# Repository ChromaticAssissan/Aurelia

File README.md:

HEAD
\# Aurelia Upper Ocean Profiler

A custom variable buoyancy ocean profiling system developed at UMass Dartmouth.

\## Features

\- Arduino-based motherboard

\- Sensor integration

\- Wireless communication

\- Variable buoyancy control

\- Custom PCB development

\## Author

Frankie Bouchard

=======
# Aurelia
The design of the control boards for the Aurelia ocean profilier
2aa0dd996f78106de7114200720a692faca2b326

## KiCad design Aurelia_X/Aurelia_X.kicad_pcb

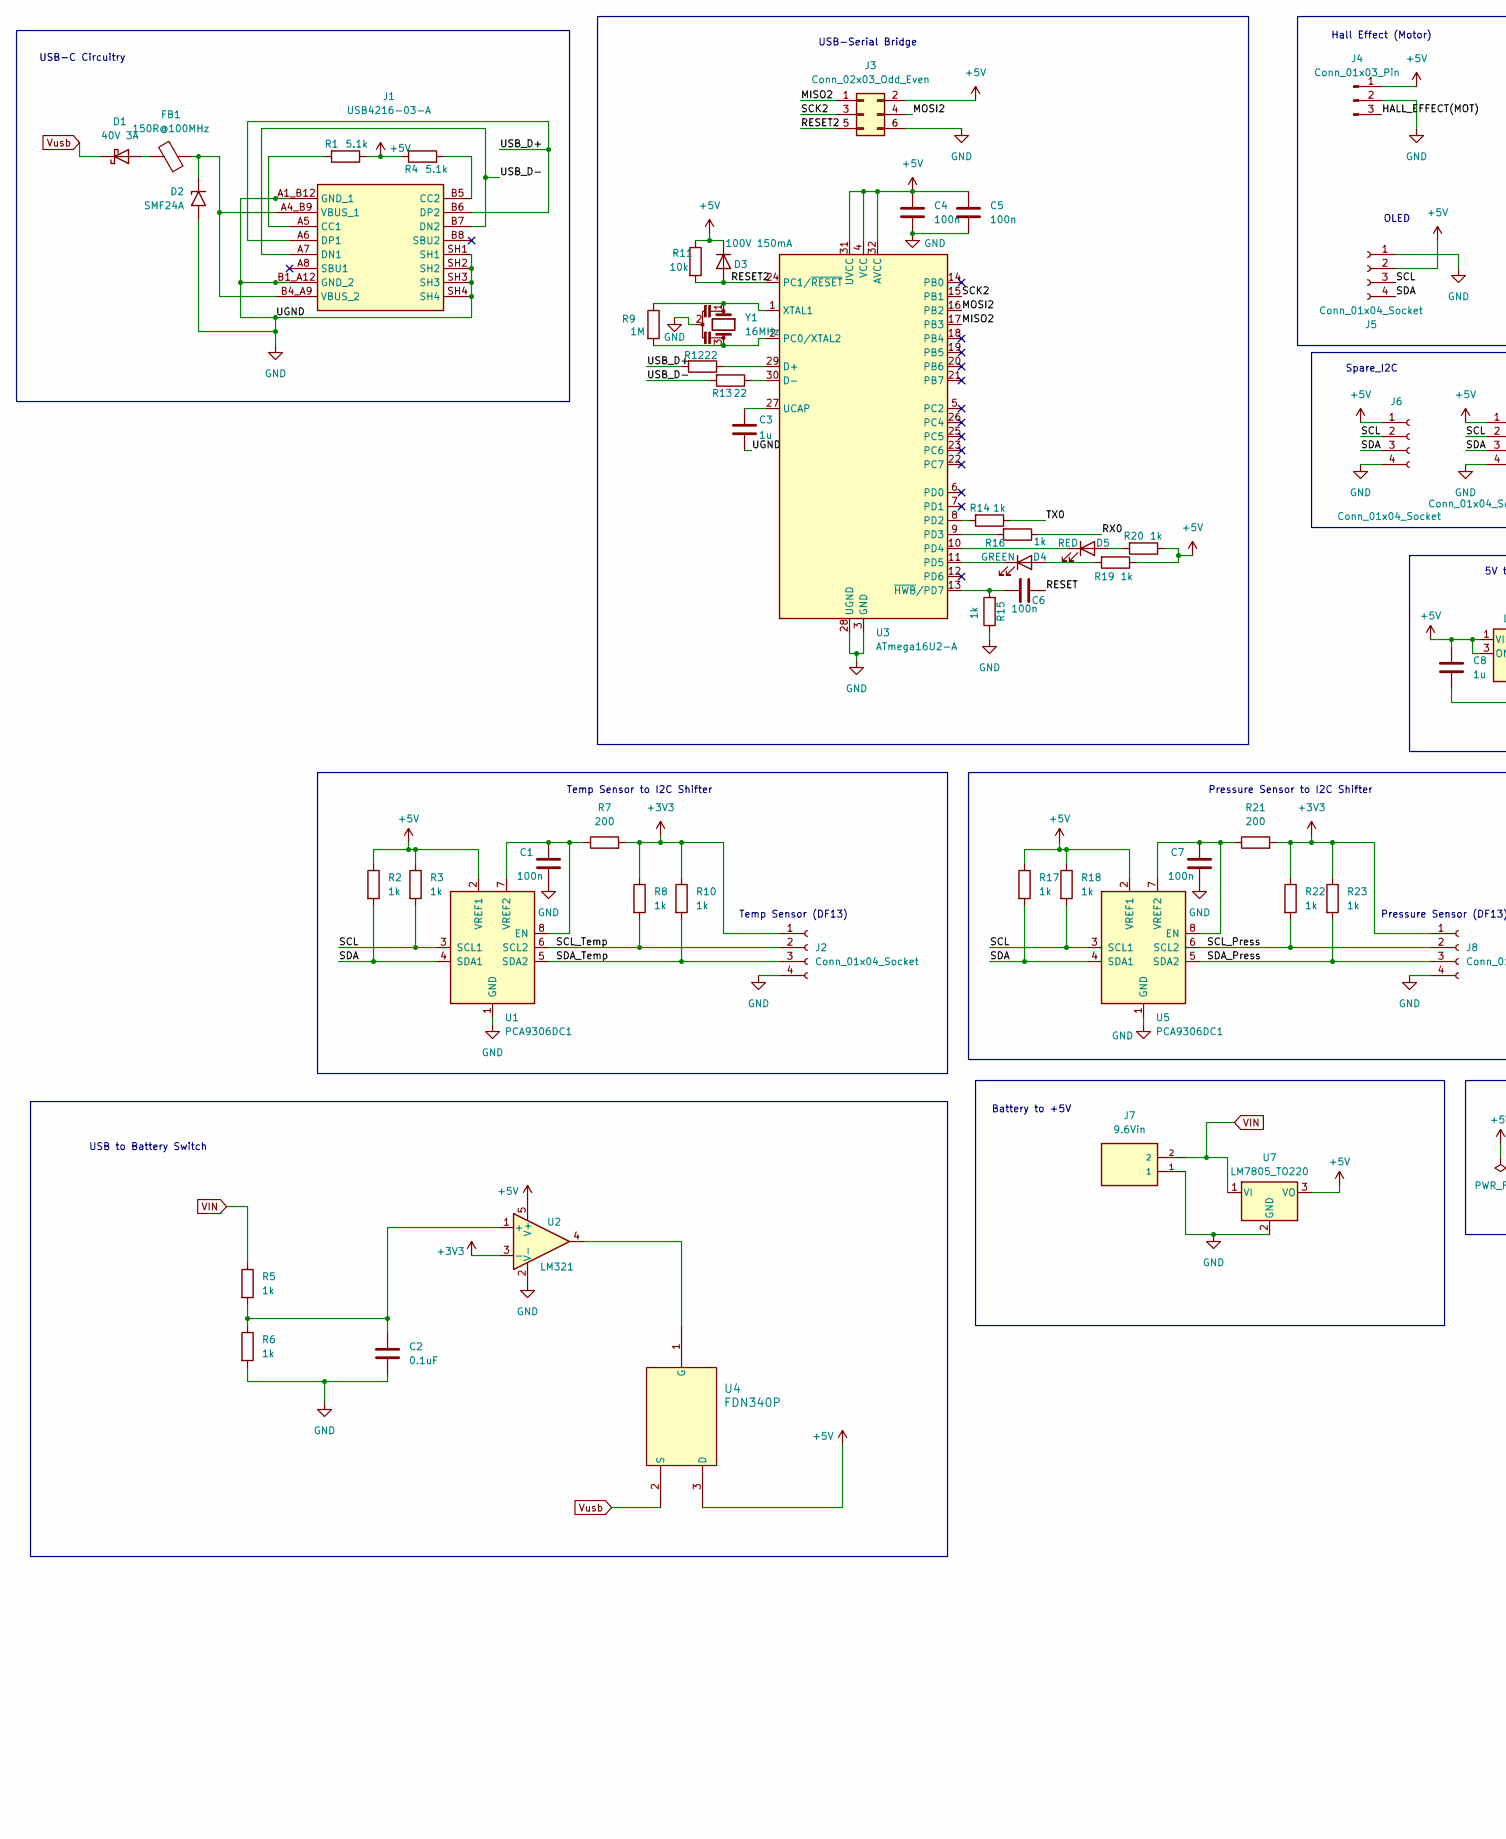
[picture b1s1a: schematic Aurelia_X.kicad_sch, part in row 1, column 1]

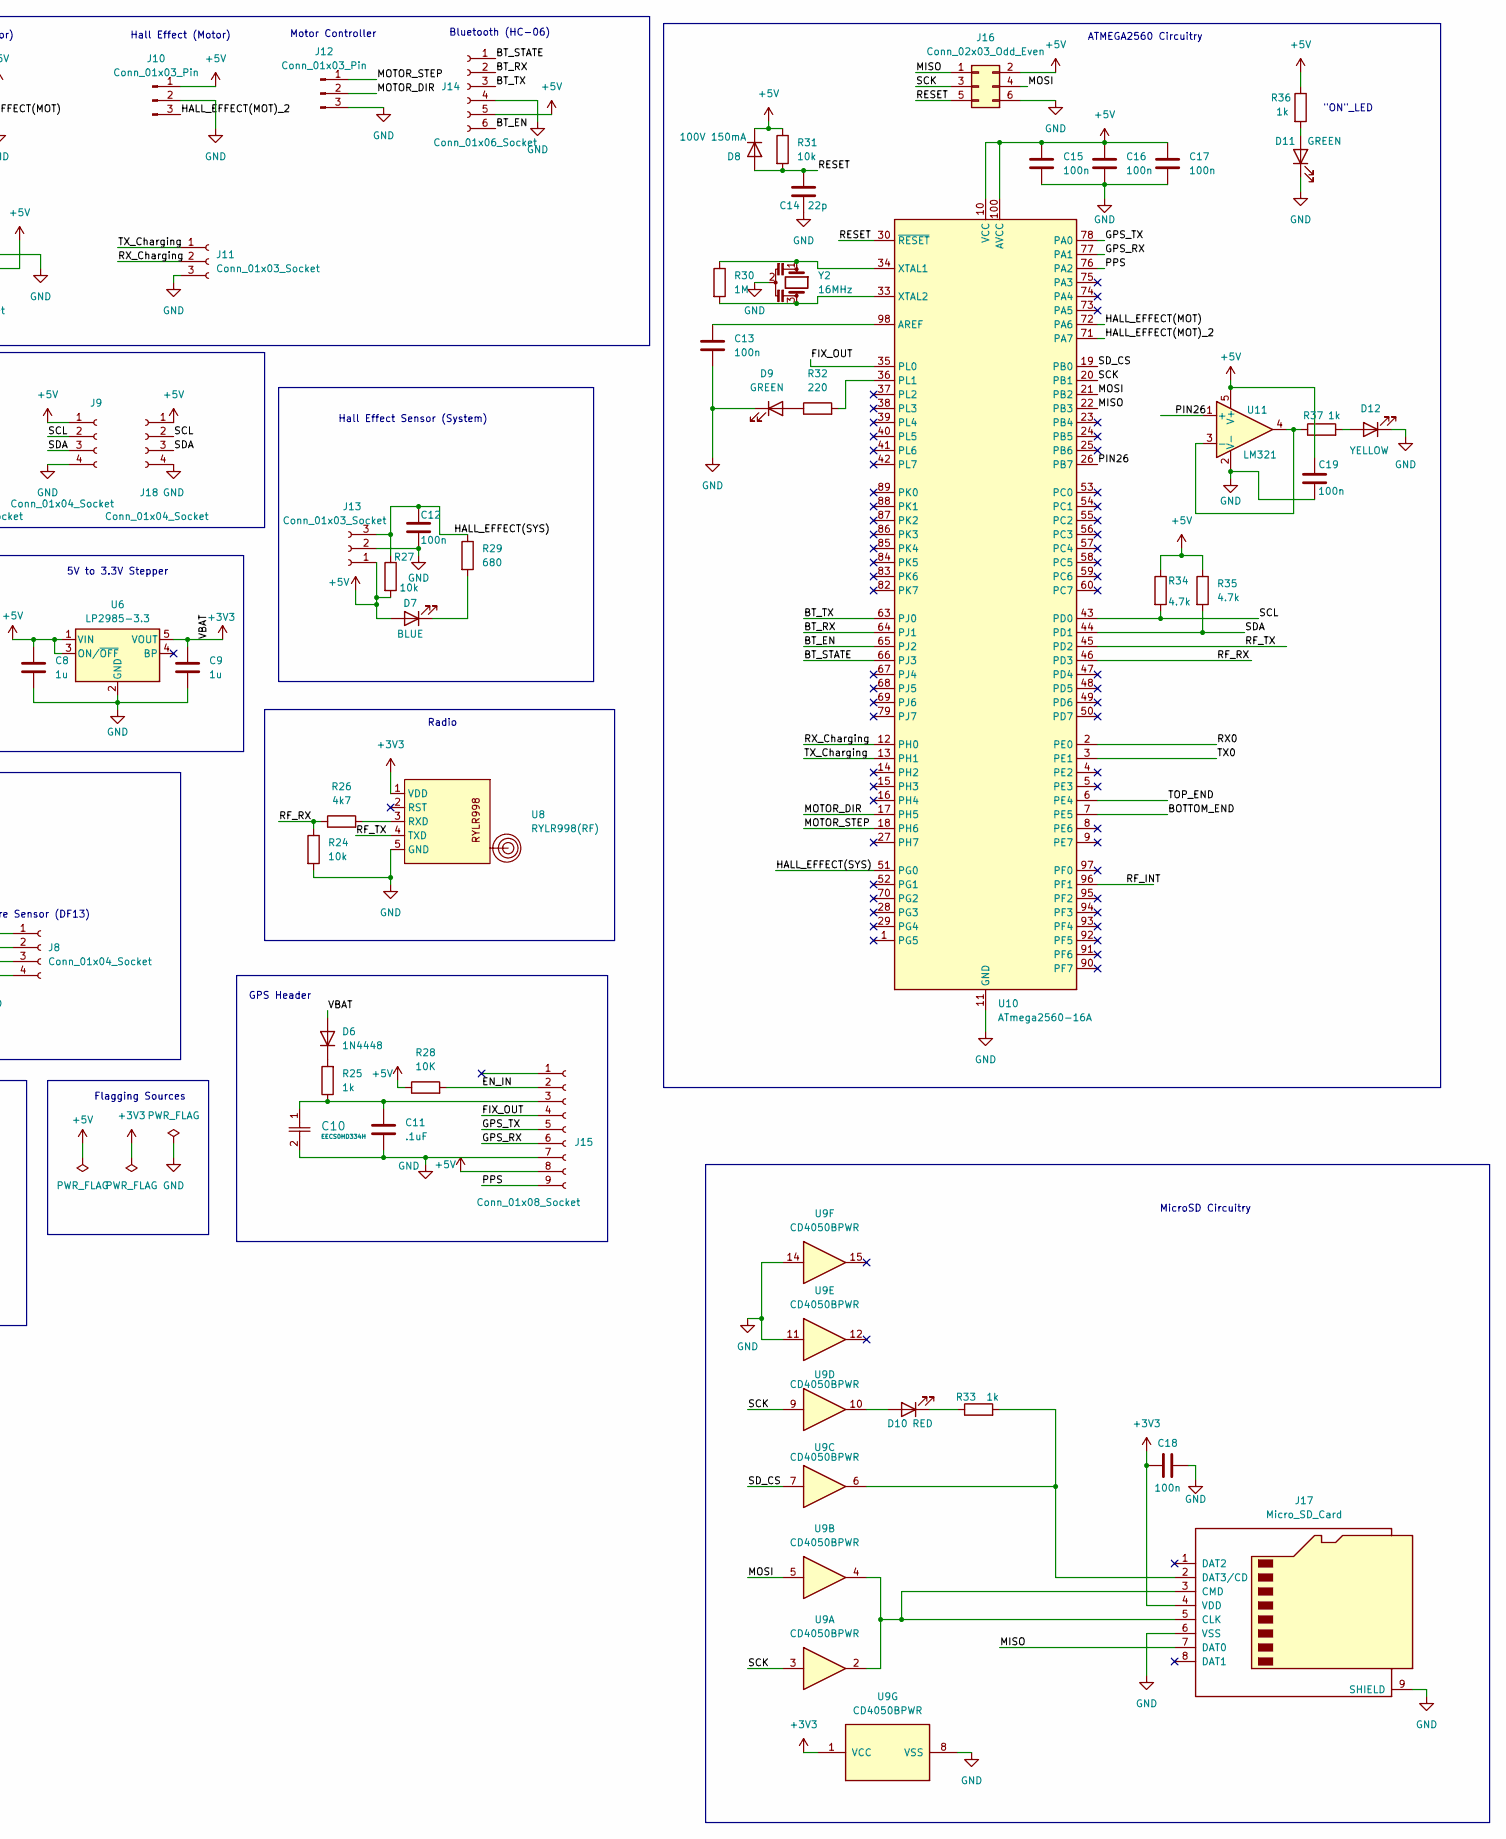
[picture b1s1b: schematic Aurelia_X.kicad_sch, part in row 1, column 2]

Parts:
C1, C4, C5, C6, C7, C12, C13, C15, C16, C17, C18, C19: 100n; C_0603_1608Metric_Pad1.08x0.95mm_HandSolder
C2: 0.1uF; C_0603_1608Metric_Pad1.08x0.95mm_HandSolder
C3, C8, C9: 1u; C_0603_1608Metric_Pad1.08x0.95mm_HandSolder
C10: EECS0HD334H; SUP_CAP_EECSD_H_PAN
C11: .1uF; C_0603_1608Metric_Pad1.08x0.95mm_HandSolder
C14: 22p; C_0603_1608Metric_Pad1.08x0.95mm_HandSolder
D1: 40V 3A; 40V_3A_SMA_SHKY_DIODE
D2: SMF24A; D_SMF
D3, D8: 100V 150mA; D_SOD-123
D4, D9, D11: GREEN; LED_0603_1608Metric_Pad1.05x0.95mm_HandSolder
D5, D10: RED; LED_0603_1608Metric_Pad1.05x0.95mm_HandSolder
D6: 1N4448; D_SOD-323F
D7: BLUE; LED_0603_1608Metric_Pad1.05x0.95mm_HandSolder
D12: YELLOW; LED_0603_1608Metric_Pad1.05x0.95mm_HandSolder
FB1: 150R@100MHz; R_0805_2012Metric_Pad1.20x1.40mm_HandSolder
J1: USB4216-03-A; GCT_USB4216-03-A_REVA; Mouser Part Number 640-USB4216-03-A
J2, J8: Conn_01x04_Socket; DF13_4P_125DS_25
J3, J16: Conn_02x03_Odd_Even; PinHeader_2x03_P2.54mm_Vertical
J4, J10, J12: Conn_01x03_Pin; PinHeader_1x03_P2.54mm_Vertical
J5: Conn_01x04_Socket; PinSocket_1x04_P2.54mm_Vertical
J6, J9, J18: Conn_01x04_Socket; JST_XA_S04B-XASK-1N-BN_1x04_P2.50mm_Horizontal
J7: 9.6Vin; 691137710002
J11: Conn_01x03_Socket; PinHeader_1x03_P2.54mm_Vertical
J13: Conn_01x03_Socket; PinSocket_1x03_P2.54mm_Vertical
J14: Conn_01x06_Socket; PinSocket_1x06_P2.54mm_Vertical
J15: Conn_01x08_Socket; PinSocket_1x09_P2.54mm_Vertical
J17: Micro_SD_Card; microSD_HC_Hirose_DM3BT-DSF-PEJS
R1, R4: 5.1k; R_0603_1608Metric_Pad0.98x0.95mm_HandSolder
R2, R3, R5, R6, R8, R10, R14, R15, R16, R17, R18, R19, R20, R22, R23, R25, R33, R36, R37: 1k; R_0603_1608Metric_Pad0.98x0.95mm_HandSolder
R7, R21: 200; R_0603_1608Metric_Pad0.98x0.95mm_HandSolder
R9, R30: 1M; R_0603_1608Metric_Pad0.98x0.95mm_HandSolder
R11, R24, R27, R31: 10k; R_0603_1608Metric_Pad0.98x0.95mm_HandSolder
R12, R13: 22; R_0603_1608Metric_Pad0.98x0.95mm_HandSolder
R26: 4k7; R_0603_1608Metric_Pad0.98x0.95mm_HandSolder
R28: 10K; R_0603_1608Metric_Pad0.98x0.95mm_HandSolder
R29: 680; R_0603_1608Metric_Pad0.98x0.95mm_HandSolder
R32: 220; R_0603_1608Metric_Pad0.98x0.95mm_HandSolder
R34, R35: 4.7k; R_0603_1608Metric_Pad0.98x0.95mm_HandSolder
U1, U5: PCA9306DC1; VSSOP-8_2.3x2mm_P0.5mm
U2, U11: LM321; SOT-23-5
U3: ATmega16U2-A; TQFP-32_7x7mm_P0.8mm
U4: FDN340P; SOT-23
U6: LP2985-3.3; SOT-23-5_HandSoldering
U7: LM7805_TO220; TO-220-3_Vertical
U8: RYLR998(RF); PinSocket_1x05_P2.54mm_Horizontal
U9: CD4050BPWR; SOIC-16_3.9x9.9mm_P1.27mm
U10: ATmega2560-16A; TQFP-100_14x14mm_P0.5mm
Y1, Y2: 16MHz; Resonator_Murata_CSTLSxxxX-3Pin_W5.5mm_H3.0mm

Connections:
+3V3: C9.1, C18.1, D6.2 (A), J2.1, J8.1, J17.4 (VDD), R7.2, R8.1, R10.1, R21.2, R22.1, R23.1, U2.3 (-), U6.5 (VOUT), U8.1 (VDD), U9.1 (VCC)
+5V: C4.1, C5.1, C8.1, C15.1, C16.1, C17.1, C19.1, D3.1 (K), D7.2 (A), D8.1 (K), J3.2, J4.1, J5.2, J6.1, J9.1, J10.1, J13.1, J14.5, J15.8, J16.2, J18.1, R1.1, R2.1, R3.1, R4.1, R11.1, R17.1, R18.1, R19.1, R20.1, R27.2, R28.1, R31.1, R34.1, R35.1, R36.1, U1.2 (VREF1), U2.5 (V+), U3.4 (VCC), U3.31 (UVCC), U3.32 (AVCC), U4.3 (D), U5.2 (VREF1), U6.1 (VIN), U6.3 (ON/~OFF), U7.3 (VO), U10.10 (VCC), U10.31 (VCC), U10.61 (VCC), U10.80 (VCC), U10.100 (AVCC), U11.5 (V+)
/BOTTOM_END: U10.7 (PE5)
/BT_EN: J14.6, U10.65 (PJ2)
/BT_RX: J14.2, U10.64 (PJ1)
/BT_STATE: J14.1, U10.66 (PJ3)
/BT_TX: J14.3, U10.63 (PJ0)
/EN_IN: J15.2, R28.2
/FIX_OUT: J15.4, U10.35 (PL0)
/GPS_RX: J15.6, U10.77 (PA1)
/GPS_TX: J15.5, U10.78 (PA0)
/HALL_EFFECT(MOT): J4.3, U10.72 (PA6)
/HALL_EFFECT(MOT)_2: J10.3, U10.71 (PA7)
/HALL_EFFECT(SYS): C12.1, J13.3, R27.1, R29.1, U10.51 (PG0)
/MISO: J16.1, J17.7 (DAT0), U10.22 (PB3)
/MISO2: J3.1, U3.17 (PB3)
/MOSI: J16.4, U9.5, U10.21 (PB2)
/MOSI2: J3.4, U3.16 (PB2)
/MOTOR_DIR: J12.2, U10.17 (PH5)
/MOTOR_STEP: J12.1, U10.18 (PH6)
/PIN26: U10.26 (PB7), U11.1 (+)
/PPS: J15.9, U10.76 (PA2)
/RESET: C6.1, C14.1, D8.2 (A), J16.5, R31.2, U10.30 (~RESET)
/RESET2: D3.2 (A), J3.5, R11.2, U3.24 (PC1/~RESET)
/RF_INT: U10.96 (PF1)
/RF_RX: R24.1, R26.1, U10.46 (PD3)
/RF_TX: U8.4 (TXD), U10.45 (PD2)
/RX0: R16.1, U10.2 (PE0)
/RX_Charging: J11.2, U10.12 (PH0)
/SCK: J16.3, U9.3, U9.9, U10.20 (PB1)
/SCK2: J3.3, U3.15 (PB1)
/SCL: J5.3, J6.2, J9.2, J18.2, R3.2, R18.2, R34.2, U1.3 (SCL1), U5.3 (SCL1), U10.43 (PD0)
/SCL_Press: J8.2, R22.2, U5.6 (SCL2)
/SCL_Temp: J2.2, R8.2, U1.6 (SCL2)
/SDA: J5.4, J6.3, J9.3, J18.3, R2.2, R17.2, R35.2, U1.4 (SDA1), U5.4 (SDA1), U10.44 (PD1)
/SDA_Press: J8.3, R23.2, U5.5 (SDA2)
/SDA_Temp: J2.3, R10.2, U1.5 (SDA2)
/SD_CS: U9.7, U10.19 (PB0)
/TOP_END: U10.6 (PE4)
/TX0: R14.1, U10.3 (PE1)
/TX_Charging: J11.1, U10.13 (PH1)
/USB_D+: J1.A6 (DP1), J1.B6 (DP2), R12.2
/USB_D-: J1.A7 (DN1), J1.B7 (DN2), R13.2
GND: C1.2, C2.2, C3.2, C4.2, C5.2, C7.2, C8.2, C9.2, C10.2, C11.2, C12.2, C13.2, C14.2, C15.2, C16.2, C17.2, C18.2, C19.2, D2.2 (A2), D9.1 (K), D11.1 (K), D12.1 (K), J1.A1_B12 (GND_1), J1.B1_A12 (GND_2), J1.SH1, J1.SH2, J1.SH3, J1.SH4, J2.4, J3.6, J4.2, J5.1, J6.4, J7.1, J8.4, J9.4, J10.2, J11.3, J12.3, J13.2, J14.4, J15.7, J16.6, J17.6 (VSS), J17.9 (SHIELD), J18.4, R6.2, R15.1, R24.2, U1.1 (GND), U2.2 (V-), U3.3 (GND), U3.28 (UGND), U5.1 (GND), U6.2 (GND), U7.2 (GND), U8.5 (GND), U9.8 (VSS), U9.11, U9.14, U10.11 (GND), U10.32 (GND), U10.62 (GND), U10.81 (GND), U10.99 (GND), U11.2 (V-), Y1.2, Y2.2
unnamed: D1.2 (A), FB1.2
unnamed: D2.1 (A1), FB1.1, J1.A4_B9 (VBUS_1), J1.B4_A9 (VBUS_2)
unnamed: D4.2 (A), R19.2
unnamed: D4.1 (K), U3.11 (PD5)
unnamed: D5.2 (A), R20.2
unnamed: D5.1 (K), U3.10 (PD4)
unnamed: D6.1 (K), R25.2
unnamed: D7.1 (K), R29.2
unnamed: D9.2 (A), R32.1
unnamed: D10.2 (A), U9.10
unnamed: D10.1 (K), R33.1
unnamed: D11.2 (A), R36.2
unnamed: D12.2 (A), R37.2
unnamed: J1.A5 (CC1), R1.2
unnamed: J1.B5 (CC2), R4.2
unnamed: C10.1, C11.1, J15.3, R25.1
unnamed: J17.3 (CMD), J17.5 (CLK), U9.2, U9.4
unnamed: J17.2 (DAT3/CD), R33.2, U9.6
unnamed: C1.1, R7.1, U1.7 (VREF2), U1.8 (EN)
unnamed: C2.1, R5.2, R6.1, U2.1 (+)
unnamed: R12.1, U3.29 (D+)
unnamed: R13.1, U3.30 (D-)
unnamed: R9.2, U3.2 (PC0/XTAL2), Y1.3
unnamed: R14.2, U3.8 (PD2)
unnamed: R16.2, U3.9 (PD3)
unnamed: C3.1, U3.27 (UCAP)
unnamed: R9.1, U3.1 (XTAL1), Y1.1
unnamed: C6.2, R15.2, U3.13 (~HWB/PD7)
unnamed: U2.4, U4.1 (G)
unnamed: C7.1, R21.1, U5.7 (VREF2), U5.8 (EN)
unnamed: R26.2, U8.3 (RXD)
unnamed: C13.1, U10.98 (AREF)
unnamed: R32.2, U10.36 (PL1)
unnamed: R30.1, U10.34 (XTAL1), Y2.1
unnamed: R30.2, U10.33 (XTAL2), Y2.3
unnamed: R37.1, U11.3 (-), U11.4
VIN: J7.2, R5.1, U7.1 (VI)
Vusb: D1.1 (K), U4.2 (S)

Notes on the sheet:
Temp Sensor (DF13)
Spare_I2C
Radio
USB-C Circuitry
Bluetooth (HC-06)
Pressure Sensor to I2C Shifter
OLED
Hall Effect Sensor (System)
Flagging Sources
ATMEGA2560 Circuitry
Motor Controller
Hall Effect (Motor)
5V to 3.3V Stepper
Battery to +5V
Pressure Sensor (DF13)
"ON"_LED
USB to Battery Switch
Temp Sensor to I2C Shifter
GPS Header
USB-Serial Bridge
MicroSD Circuitry

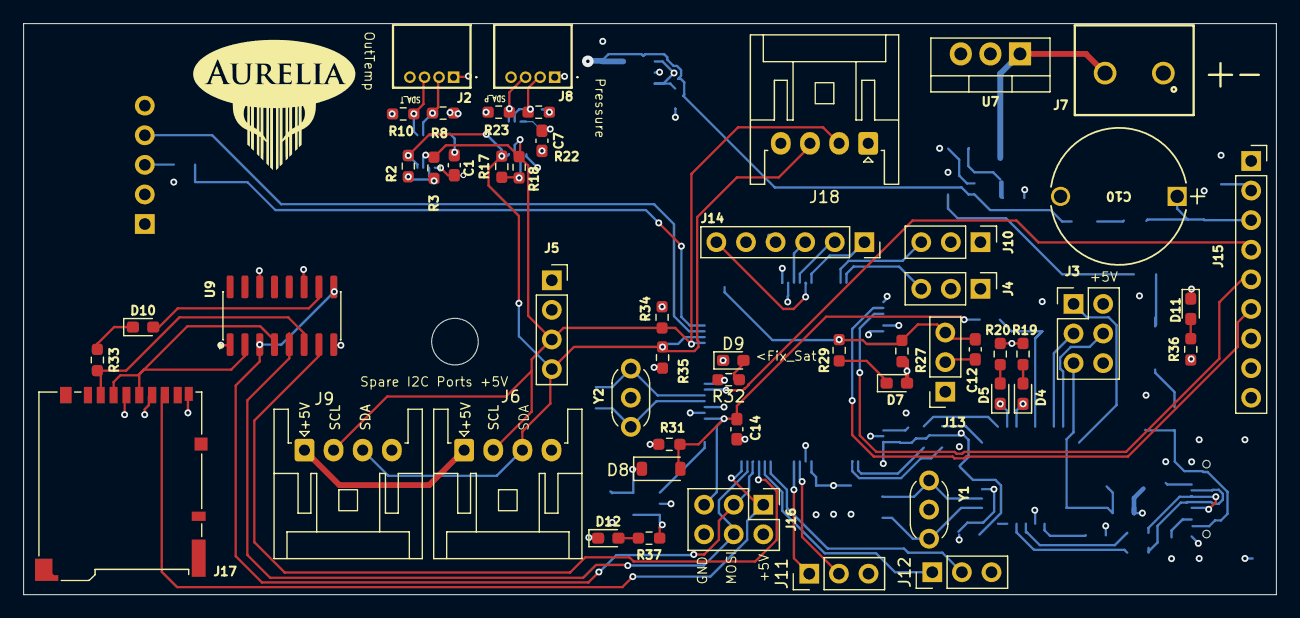
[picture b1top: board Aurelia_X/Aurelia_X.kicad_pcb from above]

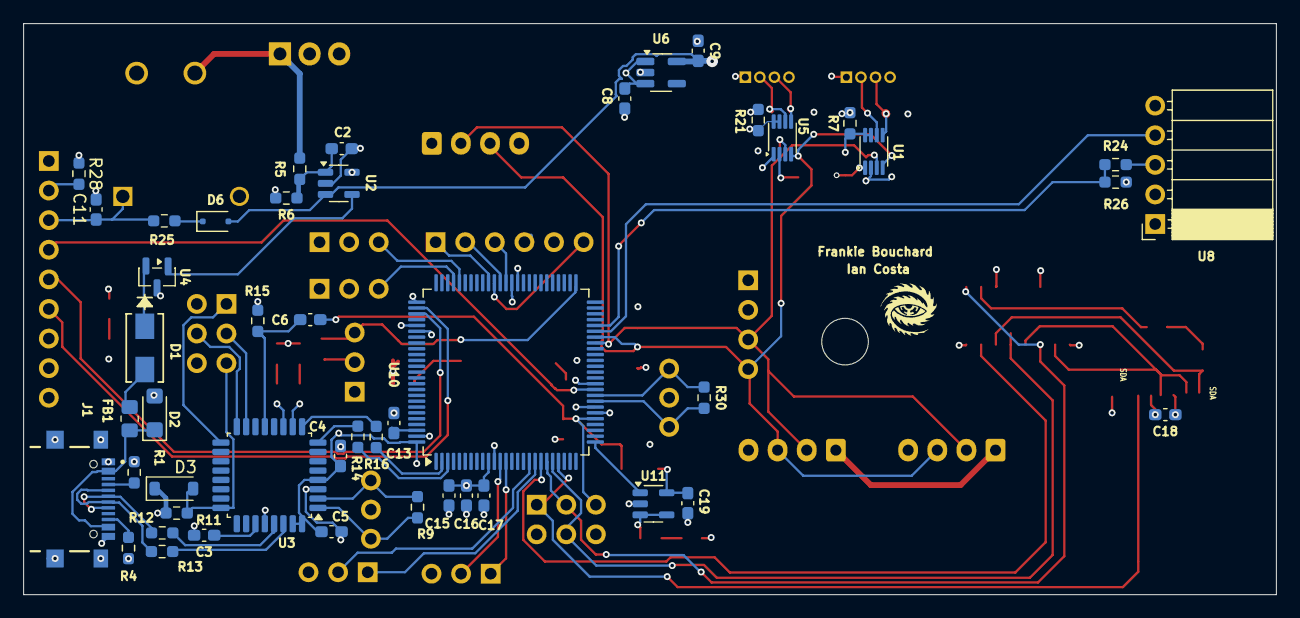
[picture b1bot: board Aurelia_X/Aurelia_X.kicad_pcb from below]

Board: 4 copper layers, 107.5 x 49.0 mm, 100 parts (47 on the bottom side), 79 nets.

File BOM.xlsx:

Refrence | Qty | Value | Footprint | Price Per | Total Price | Link
C1,C2,C4,C5,C6,C7,C11,C12,C13,C15,C16,C17,C18,C19 | 50 | 100n | Capacitor_SMD:C_0603_1608Metric_Pad1.08x0.95mm_HandSolder | 0.155 | 7.75 | https://www.digikey.com/en/products/detail/samsung-electro-m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
C3,C8,C9 | 50 | 1u | Capacitor_SMD:C_0603_1608Metric_Pad1.08x0.95mm_HandSolder | 2.5000000000000001E-2 | 1.25 | https://www.digikey.com/en/products/detail/samsung-electro-m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
C10 | 5 | EDC334Z5R5H | Aurelia Library:SUP_CAP_EECSD_H_PAN | 3.52 | 17.600000000000001 | https://www.digikey.com/en/products/detail/cornell-dubilier-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
C14 | 50 | 22p | Capacitor_SMD:C_0603_1608Metric_Pad1.08x0.95mm_HandSolder | 0.05 | 2.5 | https://www.digikey.com/en/products/detail/kemet/C0603C220J5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
D1 | 10 | 40V 3A | Aurelia Library:40V_3A_SMA_SHKY_DIODE | 0.34499999999999997 | 3.4499999999999997 | https://www.digikey.com/en/products/detail/diodes-incorporat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
D2 | 10 | SMF24A | Diode_SMD:D_SMF | 0.16400000000000001 | 1.6400000000000001 | https://www.digikey.com/en/products/detail/diotec-semiconduc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
D3,D8 | 10 | 100V 150mA | Diode_SMD:D_SOD-123 | 0.108 | 1.08 | https://www.digikey.com/en/products/detail/diotec-semiconduc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
D4,D9,D11 | 50 | GREEN | LED_SMD:LED_0603_1608Metric_Pad1.05x0.95mm_HandSolder | 6.4000000000000001E-2 | 3.2 | https://www.digikey.com/en/products/detail/liteon/LTST-C190K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
D5,D10 | 50 | RED | LED_SMD:LED_0603_1608Metric_Pad1.05x0.95mm_HandSolder | 6.4000000000000001E-2 | 3.2 | https://www.digikey.com/en/products/detail/liteon/LTST-C190K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
D6 | 10 | 1N4448WS | Diode_SMD:D_SOD-323F | 0.104 | 1.04 | https://www.digikey.com/en/products/detail/onsemi/1N4448WS/1873806
D7 | 20 | BLUE | LED_SMD:LED_0603_1608Metric_Pad1.05x0.95mm_HandSolder | 0.16 | 3.2 | https://www.digikey.com/en/products/detail/w%C3%BCrth-elektr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
D12 | 20 | YELLOW | LED_SMD:LED_0603_1608Metric_Pad1.05x0.95mm_HandSolder | 7.0000000000000007E-2 | 1.4000000000000001 | https://www.digikey.com/en/products/detail/liteon/LTST-C190K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
FB1 | 10 | 150R@100MHz | Resistor_SMD:R_0805_2012Metric_Pad1.20x1.40mm_HandSolder | 5.8000000000000003E-2 | 0.58000000000000007 | https://www.digikey.com/en/products/detail/abracon-llc/ACML-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
J1 | 10 | USB4216-03-A | MotherboardLibrary:GCT_USB4216-03-A_REVA | 0.54 | 5.4 | https://www.digikey.com/en/products/detail/gct/USB4216-03-A/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
J2,J8 | 4 | Conn_01x04_Socket | Aurelia Library:DF13_4P_125DS_25 | 0.54 | 2.16 | https://www.digikey.com/en/products/detail/hirose-electric-c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
J3,J16 | 12 | Conn_02x03_Odd_Even | Connector_PinHeader_2.54mm:PinHeader_2x03_P2.54mm_Vertical | 0.12 | 1.44 | https://www.digikey.com/en/products/detail/oupiin/2011-2X03G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
J5 | 10 | Conn_01x03_Pin | Connector_PinHeader_2.54mm:PinHeader_1x03_P2.54mm_Vertical | 0.26 | 2.6 | https://www.digikey.com/en/products/detail/adam-tech/PH1-20-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
J6,J9,J11 | 50 | Conn_01x04_Socket | Connector_JST:JST_XA_S04B-XASK-1N-BN_1x04_P2.50mm_Horizontal | 0.25700000000000001 | 12.85 | https://www.digikey.com/en/products/detail/hirose-electric-c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
J4,J10,J12,J13,J14,J15,J18 | 15 | Conn_01x20_Socket | Connector_PinSocket_2.54mm:PinSocket_1x04_P2.54mm_Vertical | 0.88 | 13.2 | https://www.digikey.com/en/products/detail/w%C3%BCrth-elektr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
J7 | 10 | 9.6Vin | MotherboardLibrary:691137710002 | 0.35399999999999998 | 3.54 | https://www.digikey.com/en/products/detail/w%C3%BCrth-elektr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
J17 | 5 | Micro_SD_Card | Connector_Card:microSD_HC_Hirose_DM3BT-DSF-PEJS | 2.52 | 12.6 | https://www.digikey.com/en/products/detail/hirose-electric-c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
R1,R4 | 10 | 5.1k | Resistor_SMD:R_0603_1608Metric_Pad0.98x0.95mm_HandSolder | 0.1 | 1 | https://www.digikey.com/en/products/detail/yageo/RC0603FR-07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
R2,R3,R5,R6,R8,R10,R14,R15,R16,R17,R18,R19,R20,R22,R23,R25,R33,R36,R37 | 19 | 1k | Resistor_SMD:R_0603_1608Metric_Pad0.98x0.95mm_HandSolder | 0.1 | 1.9000000000000001 | https://www.digikey.com/en/products/detail/stackpole-electro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
R7,R21 | 20 | 210 | Resistor_SMD:R_0603_1608Metric_Pad0.98x0.95mm_HandSolder | 0.1 | 2 | https://www.digikey.com/en/products/detail/panasonic-industr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
R9,R30 | 20 | 1M | Resistor_SMD:R_0603_1608Metric_Pad0.98x0.95mm_HandSolder | 0.1 | 2 | https://www.digikey.com/en/products/detail/yageo/RC0201FR-07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
R11,R24,R27,R28,R31 | 20 | 10k | Resistor_SMD:R_0603_1608Metric_Pad0.98x0.95mm_HandSolder | 0.1 | 2 | https://www.digikey.com/en/products/detail/yageo/RC0201FR-07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
R12,R13 | 20 | 22 | Resistor_SMD:R_0603_1608Metric_Pad0.98x0.95mm_HandSolder | 0.1 | 2 | https://www.digikey.com/en/products/detail/panasonic-industr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 | https://www.digikey.com/en/products/detail/panasonic-industr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
R26 | 20 | 4k7 | Resistor_SMD:R_0603_1608Metric_Pad0.98x0.95mm_HandSolder | 0.1 | 2 | https://www.digikey.com/en/products/detail/yageo/RC0603FR-07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
R29 | 20 | 680 | Resistor_SMD:R_0603_1608Metric_Pad0.98x0.95mm_HandSolder | 0.1 | 2 | https://www.digikey.com/en/products/detail/panasonic-industr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
R32 | 20 | 220 | Resistor_SMD:R_0603_1608Metric_Pad0.98x0.95mm_HandSolder | 0.1 | 2 | https://www.digikey.com/en/products/detail/panasonic-industr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
R34,R35 | 20 | 4.7k | Resistor_SMD:R_0603_1608Metric_Pad0.98x0.95mm_HandSolder | 0.1 | 2 | https://www.digikey.com/en/products/detail/stackpole-electro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
U1,U5 | 25 | PCA9306DC1Z | Package_SO:VSSOP-8_2.3x2mm_P0.5mm | 0.73599999999999999 | 18.399999999999999 | https://www.digikey.com/en/products/detail/nxp-usa-inc/PCA93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
U2,U11 | 25 | LM321 | Package_TO_SOT_SMD:SOT-23-5 | 5.4800000000000001E-2 | 1.37 | https://www.digikey.com/en/products/detail/shenzhen-slkormic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
U3 | 10 | ATmega16U2-A | Package_QFP:TQFP-32_7x7mm_P0.8mm | 3.24 | 32.400000000000006 | https://www.digikey.com/en/products/detail/microchip-technol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
U4 | 10 | FDN340P | Package_TO_SOT_SMD:SOT-23 | 0.39500000000000002 | 3.95 | https://www.digikey.com/en/products/detail/onsemi/FDN340P/965304
U6 | 10 | LP2985-3.3 | Package_TO_SOT_SMD:SOT-23-5_HandSoldering | 0.38200000000000001 | 3.8200000000000003 | https://www.digikey.com/en/products/detail/texas-instruments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
U7 | 10 | LM7805CV | Package_TO_SOT_THT:TO-220-3_Vertical | 0.755 | 7.55 | https://www.digikey.com/en/products/detail/stmicroelectronic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
U8 | 2 | RYLR998(RF) | Connector_PinSocket_2.54mm:PinSocket_1x05_P2.54mm_Horizontal | 11.8 | 23.6 | https://www.digikey.com/en/products/detail/reyax/RYLR998/22078252
U9 | 10 | CD4050BPWR | Package_SO:SOIC-16_3.9x9.9mm_P1.27mm | 0.437 | 4.37 | https://www.digikey.com/en/products/detail/texas-instruments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
U10 | 10 | ATmega2560-16A | Package_QFP:TQFP-100_14x14mm_P0.5mm | 21.67 | 216.70000000000002 | https://www.digikey.com/en/products/detail/microchip-technol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
Y1,Y2 | 25 | 16MHz | Crystal:Resonator_Murata_CSTLSxxxX-3Pin_W5.5mm_H3.0mm | 0.27160000000000001 | 6.79 | https://www.digikey.com/en/products/detail/murata-electronic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
O1 | 4 | HC-06 | Bluetooth Module | 4.2474999999999996 | 16.989999999999998 | https://www.amazon.com/ACEIRMC-Wireless-Bluetooth-Transceive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
 |  |  |  | Total | 456.52000000000004

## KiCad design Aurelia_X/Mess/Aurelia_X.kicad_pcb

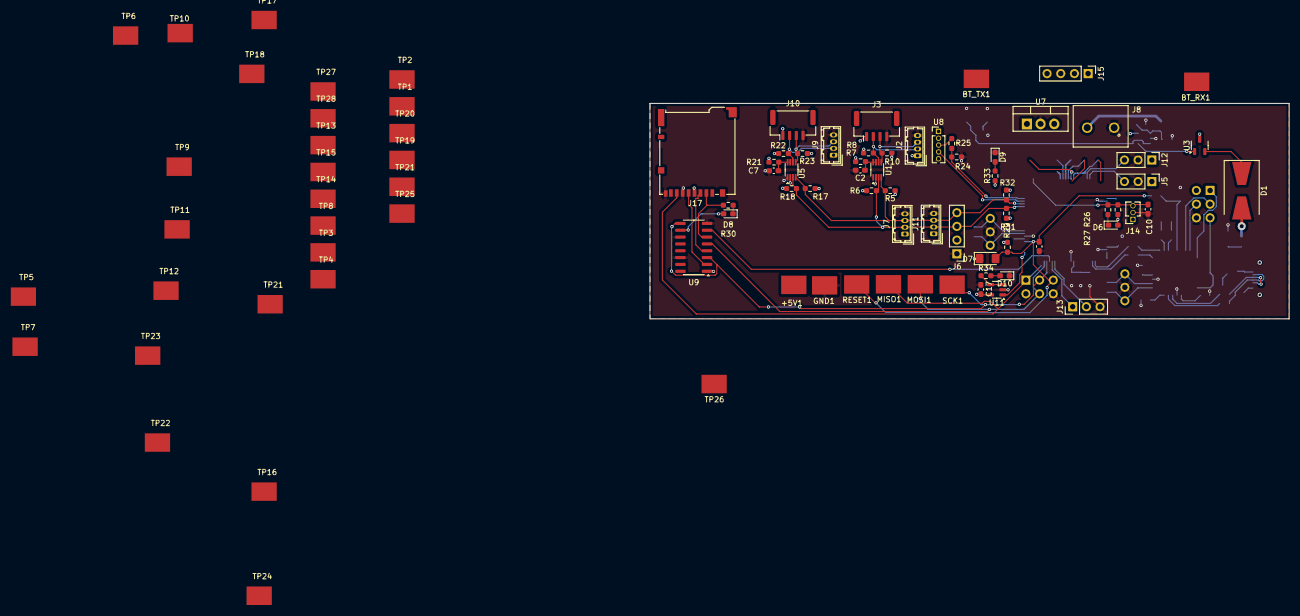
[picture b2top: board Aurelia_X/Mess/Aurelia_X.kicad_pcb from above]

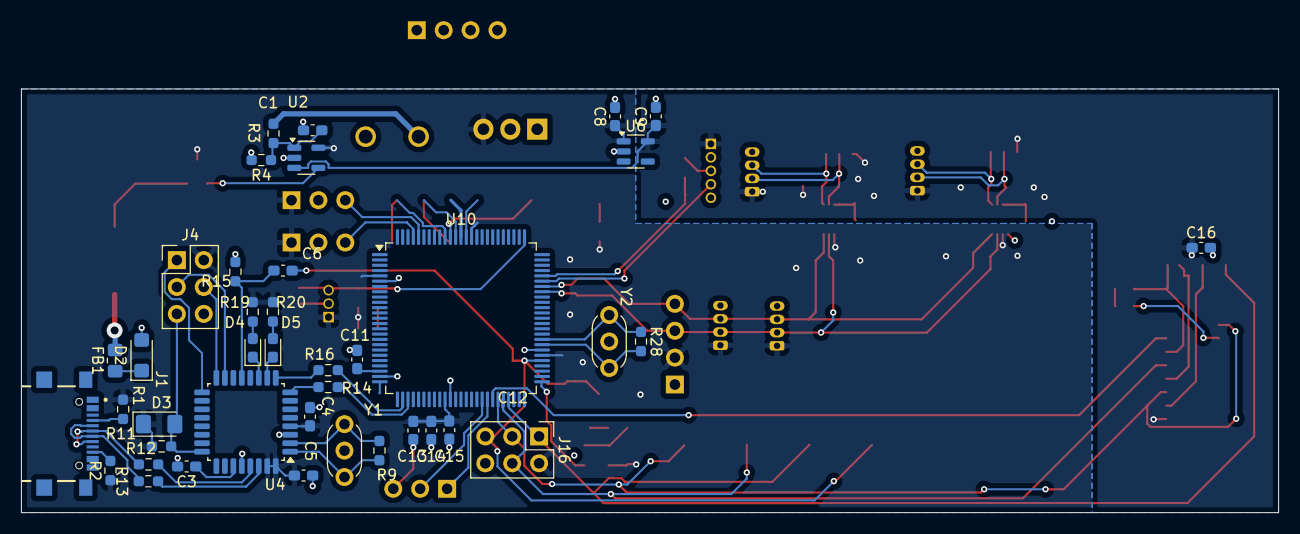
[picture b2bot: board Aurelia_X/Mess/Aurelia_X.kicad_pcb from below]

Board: 2 copper layers, 118.7 x 40.0 mm, 129 parts (40 on the bottom side), 72 nets.

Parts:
+5V1: 5018; TesPo_TP470X343
BT_RX1: 5018; TesPo_TP470X343
BT_TX1: 5018; TesPo_TP470X343
C1: 0.1uF; C_0603_1608Metric_Pad1.08x0.95mm_HandSolder
C2, C4, C5, C6, C7, C10, C11, C13, C14, C15, C16, C17: 100n; C_0603_1608Metric_Pad1.08x0.95mm_HandSolder
C3, C8, C9: 1u; C_0603_1608Metric_Pad1.08x0.95mm_HandSolder
C12: 22p; C_0603_1608Metric_Pad1.08x0.95mm_HandSolder
D1: 40V 3A; D_SMB-SMC_Universal_Handsoldering
D2: SMF24A; D_SMF
D3, D7: 100V 150mA; D_1206_3216Metric_Pad1.42x1.75mm_HandSolder
D4, D9: GREEN; LED_0603_1608Metric_Pad1.05x0.95mm_HandSolder
D5, D8: RED; LED_0603_1608Metric_Pad1.05x0.95mm_HandSolder
D6: BLUE; LED_0603_1608Metric_Pad1.05x0.95mm_HandSolder
D10: YELLOW; LED_0603_1608Metric_Pad1.05x0.95mm_HandSolder
FB1: 150R@100MHz; R_0805_2012Metric_Pad1.20x1.40mm_HandSolder
GND1: 5018; TesPo_TP470X343
J1: USB4216-03-A; GCT_USB4216-03-A_REVA
J2, J7, J9, J11: Conn_01x04_Socket; Hirose_DF13-04P-1.25DSA_1x04_P1.25mm_Vertical
J3, J10: Conn_01x04_Socket; JST_GH_BM04B-GHS-TBT_1x04-1MP_P1.25mm_Vertical
J4, J16: Conn_02x03_Odd_Even; PinHeader_2x03_P2.54mm_Vertical
J5, J12, J13: Conn_01x03_Pin; PinHeader_1x03_P2.54mm_Vertical
J6, J15: Conn_01x04_Socket; PinHeader_1x04_P2.54mm_Vertical
J8: 9.6Vin; 691137710002
J14: Conn_01x03_Socket; PinSocket_1x03_P1.27mm_Vertical
J17: Micro_SD_Card; microSD_HC_Hirose_DM3BT-DSF-PEJS
MISO1: 5018; TesPo_TP470X343
MOSI1: 5018; TesPo_TP470X343
R1, R2: 5.1k; R_0603_1608Metric_Pad0.98x0.95mm_HandSolder
R3, R4, R5, R6, R8, R10, R14, R15, R16, R17, R18, R19, R20, R22, R23, R30, R33, R34: 1k; R_0603_1608Metric_Pad0.98x0.95mm_HandSolder
R7, R21: 200; R_0603_1608Metric_Pad0.98x0.95mm_HandSolder
R9, R28: 1M; R_0603_1608Metric_Pad0.98x0.95mm_HandSolder
R11, R24, R26, R29: 10k; R_0603_1608Metric_Pad0.98x0.95mm_HandSolder
R12, R13: 22; R_0603_1608Metric_Pad0.98x0.95mm_HandSolder
R25: 4k7; R_0603_1608Metric_Pad0.98x0.95mm_HandSolder
R27: 680; R_0603_1608Metric_Pad0.98x0.95mm_HandSolder
R31, R32: 4.7k; R_0603_1608Metric_Pad0.98x0.95mm_HandSolder
RESET1: 5018; TesPo_TP470X343
SCK1: 5018; TesPo_TP470X343
TP1, TP2, TP3, TP4, TP5, TP6, TP7, TP8, TP9, TP10, TP11, TP12, TP13, TP14, TP15, TP16, TP17, TP18, TP19, TP20, TP21, TP21#2, TP22, TP23, TP24, TP25, TP26, TP27, TP28: 5018; TesPo_TP470X343
U1, U5: PCA9306DC1; VSSOP-8_2.3x2mm_P0.5mm
U2, U11: LM321; SOT-23-5
U3: FDN340P; SOT-23-3
U4: ATmega16U2-A; TQFP-32_7x7mm_P0.8mm
U6: LP2985-3.3; SOT-23-5
U7: LM7805_TO220; TO-220-3_Vertical
U8: RYLR998(RF); PinHeader_1x05_P1.27mm_Vertical
U9: 4050; SOIC-16_3.9x9.9mm_P1.27mm
U10: ATmega2560-16A; TQFP-100_14x14mm_P0.5mm
Y1, Y2: 16MHz; Resonator_Murata_CSTLSxxxX-3Pin_W5.5mm_H3.0mm

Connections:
+3V3: C9.1, C16.1, J2.1, J3.1, J9.1, J10.1, J17.4 (VDD), R7.2, R8.1, R10.1, R21.2, R22.1, R23.1, TP15.TP, U2.3 (-), U6.5 (VOUT), U8.1 (VDD), U9.1 (VCC)
+5V: +5V1.TP, C4.1, C5.1, C8.1, C13.1, C14.1, C15.1, C17.1, D3.1 (K), D6.2 (A), D7.1 (K), J4.2, J5.1, J6.2, J7.1, J11.1, J12.1, J14.1, J15.4, J16.2, R1.1, R2.1, R5.1, R6.1, R11.1, R17.1, R18.1, R19.1, R20.1, R26.2, R29.1, R31.1, R32.1, R33.1, TP9.TP, TP13.TP, U1.2 (VREF1), U2.5 (V+), U3.3 (D), U4.4 (VCC), U4.31 (UVCC), U4.32 (AVCC), U5.2 (VREF1), U6.1 (VIN), U6.3 (ON/~OFF), U7.3 (VO), U10.10 (VCC), U10.31 (VCC), U10.61 (VCC), U10.80 (VCC), U11.5 (V+)
/BOTTOM_END: TP23.TP, U10.17 (PH5)
/BT_RX: BT_RX1.TP, J15.1, U10.44 (PD1)
/BT_TX: BT_TX1.TP, J15.2, U10.43 (PD0)
/GPS_RX: TP18.TP, U10.3 (PE1)
/GPS_TX: TP17.TP, U10.2 (PE0)
/HALL_EFFECT(MOT): J5.3, TP24.TP, U10.98 (AREF)
/HALL_EFFECT(MOT)_2: J12.3, TP25.TP
/HALL_EFFECT(SYS): C10.1, J14.3, R26.1, R27.1, TP16.TP, U10.97 (PF0)
/MISO: J16.1, J17.7 (DAT0), MISO1.TP, U10.38 (PL3)
/MISO2: J4.1, TP5.TP, U4.17 (PB3)
/MOSI: J16.4, MOSI1.TP, U9.5, U10.37 (PL2)
/MOSI2: J4.4, TP10.TP, U4.16 (PB2)
/MOTOR_DIR: J13.2, TP19.TP, U10.7 (PE5)
/MOTOR_STEP: J13.1, TP20.TP, U10.8 (PE6)
/PIN26: U10.42 (PL7), U11.1 (+)
/RESET: C6.1, C12.1, D7.2 (A), J16.5, R29.2, RESET1.TP, U10.78 (PA0)
/RESET2: D3.2 (A), J4.5, R11.2, TP6.TP, U4.24 (PC1/~RESET)
/RF_INT: TP21.TP, U10.52 (PG1)
/RF_RX: R24.1, R25.1, U10.66 (PJ3)
/RF_TX: U8.4 (TXD), U10.65 (PJ2)
/RX0: R16.1, TP12.TP, U10.12 (PH0)
/SCK: J16.3, SCK1.TP, U9.3, U9.9, U10.36 (PL1)
/SCK2: J4.3, TP7.TP, U4.15 (PB1)
/SCL: J6.3, J7.2, J11.2, R6.2, R18.2, R31.2, TP28.TP, U1.3 (SCL1), U5.3 (SCL1), U10.63 (PJ0)
/SCL_Press: J9.2, J10.2, R22.2, U5.6 (SCL2)
/SCL_Temp: J2.2, J3.2, R8.2, U1.6 (SCL2)
/SDA: J6.4, J7.3, J11.3, R5.2, R17.2, R32.2, TP27.TP, U1.4 (SDA1), U5.4 (SDA1), U10.64 (PJ1)
/SDA_Press: J9.3, J10.3, R23.2, U5.5 (SDA2)
/SDA_Temp: J2.3, J3.3, R10.2, U1.5 (SDA2)
/SD_CS: U9.7, U10.35 (PL0)
/TOP_END: TP22.TP, U10.16 (PH4)
/TX0: R14.1, TP11.TP, U10.13 (PH1)
/USB_D+: J1.A6 (DP1), J1.B6 (DP2), R12.2, TP2.TP
/USB_D-: J1.A7 (DN1), J1.B7 (DN2), R13.2, TP1.TP
GND: C1.2, C2.2, C3.2, C4.2, C5.2, C7.2, C8.2, C9.2, C10.2, C11.2, C12.2, C13.2, C14.2, C15.2, C16.2, C17.2, D2.2 (A2), D9.1 (K), D10.1 (K), GND1.TP, J2.4, J3.4, J4.6, J5.2, J6.1, J7.4, J8.1, J9.4, J10.4, J11.4, J12.2, J13.3, J14.2, J15.3, J16.6, J17.6 (VSS), J17.9 (SHIELD), R4.2, R15.1, R24.2, TP26.TP, U1.1 (GND), U2.2 (V-), U4.3 (GND), U4.28 (UGND), U5.1 (GND), U6.2 (GND), U7.2 (GND), U8.5 (GND), U9.8 (VSS), U9.11, U9.14, U10.11 (GND), U10.32 (GND), U10.62 (GND), U10.81 (GND), U10.99 (GND), U11.2 (V-), Y1.2, Y2.2
unnamed: D1.2 (A), FB1.2
unnamed: D2.1 (A1), FB1.1
unnamed: D4.2 (A), R19.2
unnamed: D4.1 (K), U4.11 (PD5)
unnamed: D5.2 (A), R20.2
unnamed: D5.1 (K), U4.10 (PD4)
unnamed: D6.1 (K), R27.2
unnamed: D8.2 (A), U9.10
unnamed: D8.1 (K), R30.1
unnamed: D9.2 (A), R33.2
unnamed: D10.2 (A), R34.2
unnamed: J1.A5 (CC1), R1.2
unnamed: J1.B5 (CC2), R2.2
unnamed: J17.5 (CLK), U9.2
unnamed: J17.3 (CMD), U9.4
unnamed: J17.2 (DAT3/CD), R30.2, U9.6
unnamed: C2.1, R7.1, U1.7 (VREF2), U1.8 (EN)
unnamed: C1.1, R3.2, R4.1, TP3.TP, U2.1 (+)
unnamed: TP8.TP, U2.4, U3.1 (G)
unnamed: R12.1, U4.29 (D+)
unnamed: R13.1, U4.30 (D-)
unnamed: R9.2, U4.2 (PC0/XTAL2), Y1.3
unnamed: R14.2, U4.8 (PD2)
unnamed: R16.2, U4.9 (PD3)
unnamed: C3.1, U4.27 (UCAP)
unnamed: R9.1, U4.1 (XTAL1), Y1.1
unnamed: C6.2, R15.2, U4.13 (~HWB/PD7)
unnamed: C7.1, R21.1, U5.7 (VREF2), U5.8 (EN)
unnamed: R25.2, U8.3 (RXD)
unnamed: R28.1, U10.76 (PA2), Y2.1
unnamed: R28.2, U10.74 (PA4), Y2.3
unnamed: C11.1, U10.72 (PA6)
unnamed: R34.1, U11.3 (-), U11.4
VIN: J8.2, R3.1, TP14.TP, U7.1 (VI)
Vusb: D1.1 (K), TP4.TP, U3.2 (S)

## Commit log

2026-05-26 Initial Aurelia repository setup
2026-05-26 Added Aurelia motherboard and charging board files
2026-06-14 Create Aurelia_X
2026-06-25 Add completed Aurelia X KiCad Project
